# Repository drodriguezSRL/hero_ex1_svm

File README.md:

# HERO Explorer 1 Rover - Service Module (SVM)

The following contains all the design files (i.e., kiCad project files) for the PCBs inside the service module. That includes the Power Supply Unit (PSU), Power Distribution Unit (PDU), and the Rocker Interface Unit (RIU).  3D graphics files are also included (.step and .stl).

## Versioning

High-speed Exploration Rover Team, Explorer 1 Service Module SVM Version 1. Rev. 0.

## Authors

* **David Rodriguez** - *Head of the project*
* **Alan Allart** - *Electronics & Low-level developer*

See also a list of contributors

* **Kazuki Nakagoshi** - *Manufacturing & International relationships*
* **Tristan Lecocq** - *Power system*
* **Sayo Sugimori** - *Secretary*
* **Kazuya Yoshida** - *Professor, Space Robotics Lab*

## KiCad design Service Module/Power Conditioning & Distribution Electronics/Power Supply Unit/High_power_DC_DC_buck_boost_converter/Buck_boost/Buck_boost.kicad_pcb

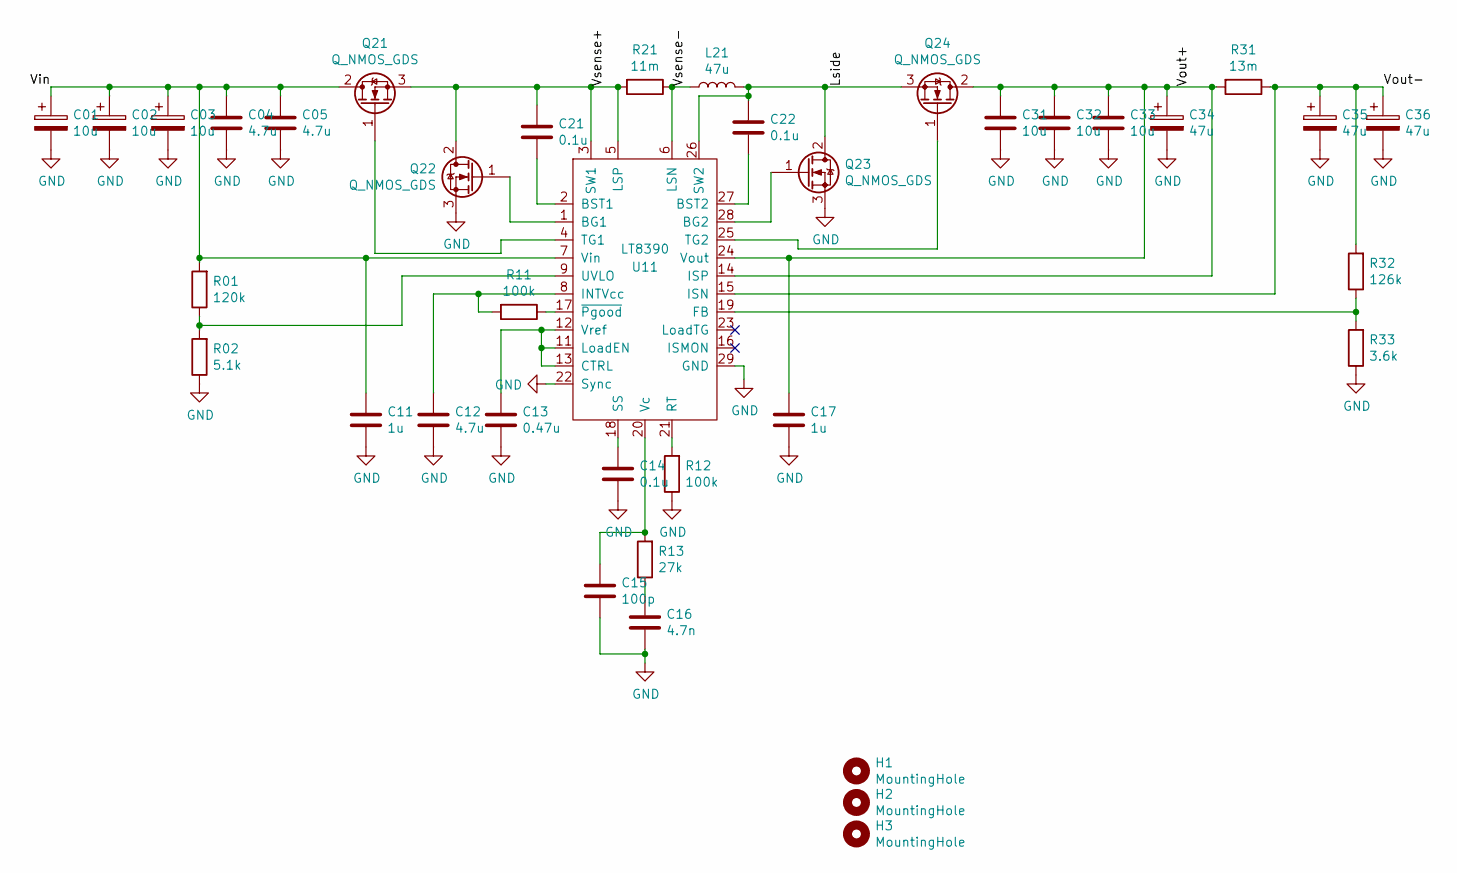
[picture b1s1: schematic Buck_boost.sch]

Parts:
C01, C02, C03: 10u; CP_Elec_8x6.5
C04, C05, C12: 4.7u; C_1206_3216Metric
C11, C17: 1u; C_0805_2012Metric
C13: 0.47u; C_0603_1608Metric
C14: 0.1u; C_0603_1608Metric
C15: 100p; C_0603_1608Metric
C16: 4.7n; C_0603_1608Metric
C21, C22: 0.1u; C_0805_2012Metric
C31, C32, C33: 10u; C_1210_3225Metric
C34, C35, C36: 47u; CP_Elec_10x10.5
H1, H2, H3: MountingHole; MountingHole_2.7mm_M2.5
L21: 47u; PA4344_333ANLT
Q21, Q22, Q23, Q24: Q_NMOS_GDS; DPAK
R01: 120k; R_0603_1608Metric
R02: 5.1k; R_0603_1608Metric
R11, R12: 100k; R_0603_1608Metric
R13: 27k; R_0603_1608Metric
R21: 11m; R_2512_6332Metric
R31: 13m; R_2512_6332Metric
R32: 126k; R_0603_1608Metric
R33: 3.6k; R_0603_1608Metric
U11: LT8390; TSSOP-28-1EP_4.4x9.7mm_P0.65mm

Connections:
/Lside: C22.1, L21.2, Q23.2 (D), Q24.3 (S), U11.26 (SW2)
/Vin: C01.1, C02.1, C03.1, C04.1, C05.1, C11.1, Q21.2 (D), R01.2, U11.7 (Vin)
/Vout+: C17.1, C31.1, C32.1, C33.1, C34.1, Q24.2 (D), R31.2, U11.14 (ISP), U11.24 (Vout)
/Vout-: C35.1, C36.1, R31.1, R32.2, U11.15 (ISN)
/Vsense+: C21.1, Q21.3 (S), Q22.2 (D), R21.2, U11.3 (SW1), U11.5 (LSP)
/Vsense-: L21.1, R21.1, U11.6 (LSN)
GND: C01.2, C02.2, C03.2, C04.2, C05.2, C11.2, C12.2, C13.2, C14.2, C15.2, C16.2, C17.2, C31.2, C32.2, C33.2, C34.2, C35.2, C36.2, Q22.3 (S), Q23.3 (S), R02.1, R12.1, R33.1, U11.22 (Sync), U11.29 (GND)
unnamed: C12.1, R11.2, U11.8 (INTVcc)
unnamed: C13.1, U11.11 (LoadEN), U11.12 (Vref), U11.13 (CTRL)
unnamed: C14.1, U11.18 (SS)
unnamed: C15.1, R13.2, U11.20 (Vc)
unnamed: C16.1, R13.1
unnamed: C21.2, U11.2 (BST1)
unnamed: C22.2, U11.27 (BST2)
unnamed: Q21.1 (G), U11.4 (TG1)
unnamed: Q22.1 (G), U11.1 (BG1)
unnamed: Q23.1 (G), U11.28 (BG2)
unnamed: Q24.1 (G), U11.25 (TG2)
unnamed: R01.1, R02.2, U11.9 (UVLO)
unnamed: R11.1, U11.17 (~Pgood)
unnamed: R12.2, U11.21 (RT)
unnamed: R32.1, R33.2, U11.19 (FB)

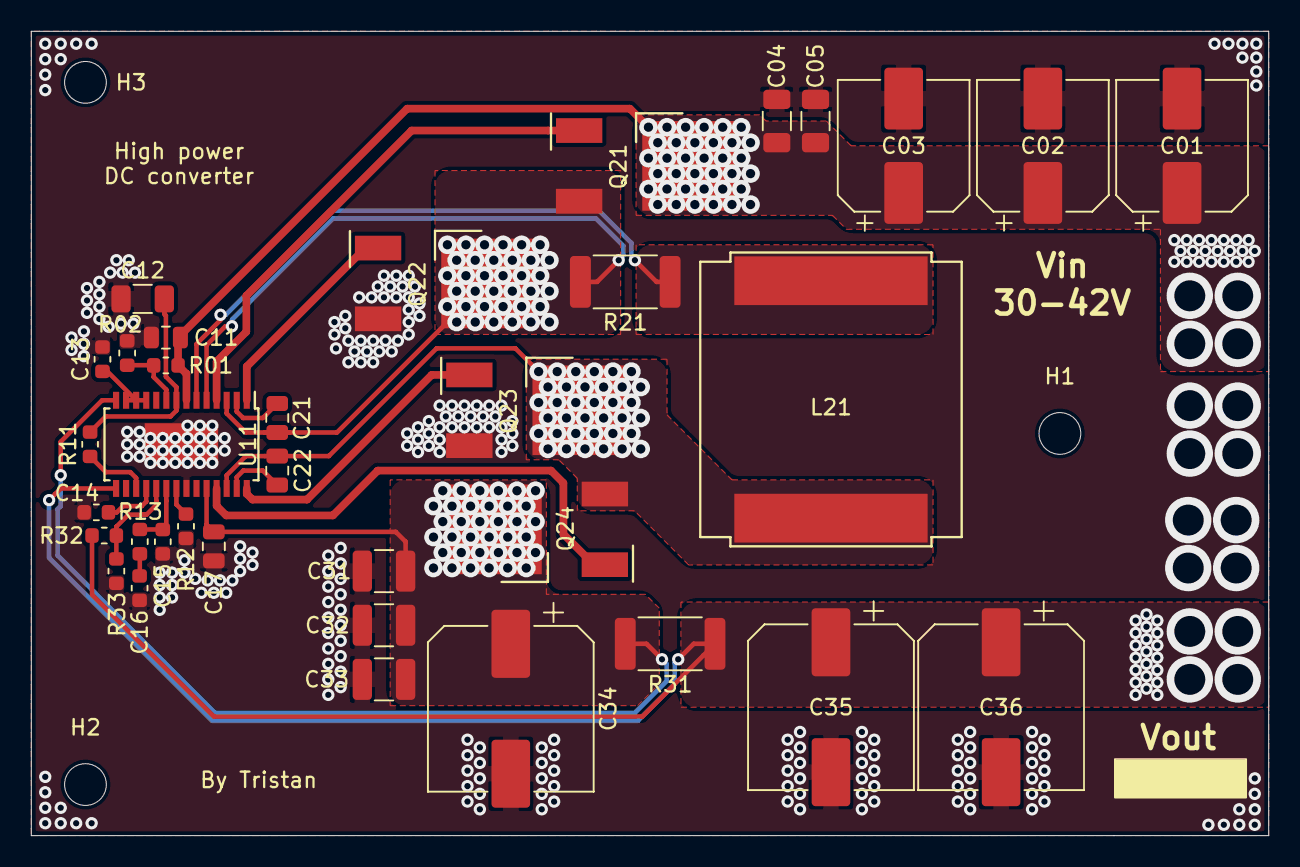
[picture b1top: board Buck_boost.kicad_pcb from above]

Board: 2 copper layers, 80.0 x 52.0 mm, 38 parts (0 on the bottom side), 22 nets.

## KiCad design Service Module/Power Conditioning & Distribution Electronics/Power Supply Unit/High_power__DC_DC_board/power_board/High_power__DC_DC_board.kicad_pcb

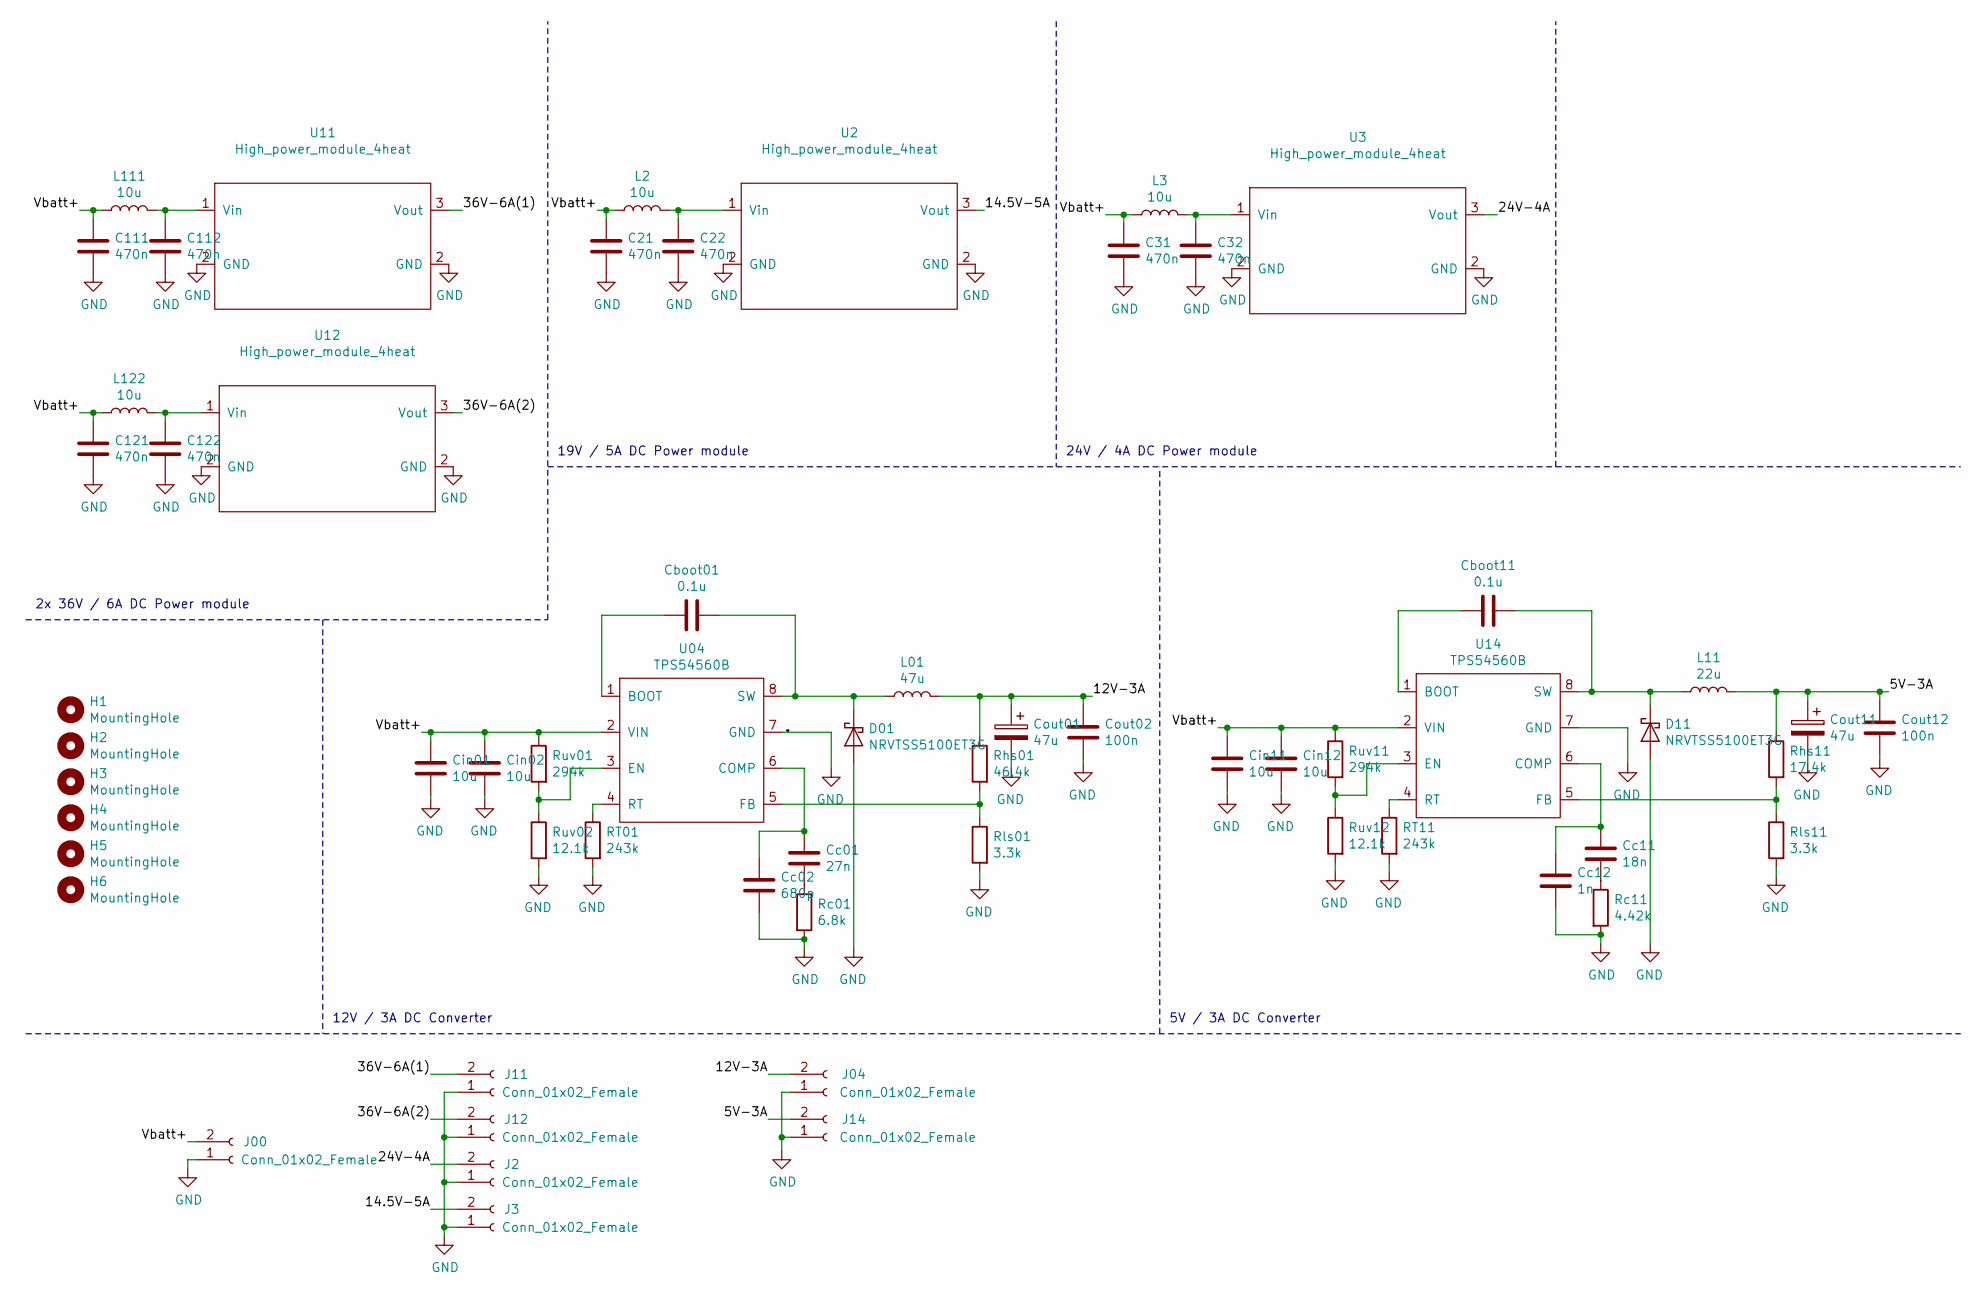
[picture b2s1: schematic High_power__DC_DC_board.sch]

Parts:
C21, C22, C31, C32, C111, C112, C121, C122: 470n; C_1210_3225Metric
Cboot01, Cboot11: 0.1u; C_0805_2012Metric
Cc01: 27n; C_0603_1608Metric
Cc02: 680p; C_0603_1608Metric
Cc11: 18n; C_0603_1608Metric
Cc12: 1n; C_0603_1608Metric
Cin01, Cin02, Cin11, Cin12: 10u; C_1210_3225Metric
Cout01, Cout11: 47u; CP_EIA-7343-40_Kemet-Y
Cout02, Cout12: 100n; C_0805_2012Metric
D01, D11: NRVTSS5100ET3G; D_SMB
H1, H2, H3, H4, H5, H6: MountingHole; MountingHole_3.2mm_M3
J00, J2, J3, J04, J11, J12, J14: Conn_01x02_Female; 172448-0004_Molex_2channel_horizontal
L01: 47u; 177CDMCC-DS
L2, L3: 10u; PA4341-XXXNLT
L11: 22u; 125CDMCCDS
L111, L122: 10u; 744373965100
RT01, RT11: 243k; R_0603_1608Metric
Rc01: 6.8k; R_0603_1608Metric
Rc11: 4.42k; R_0603_1608Metric
Rhs01: 46.4k; R_0603_1608Metric
Rhs11: 17.4k; R_0603_1608Metric
Rls01, Rls11: 3.3k; R_0603_1608Metric
Ruv01, Ruv11: 294k; R_0603_1608Metric
Ruv02, Ruv12: 12.1k; R_0603_1608Metric
U2, U3, U11, U12: High_power_module_4heat; DC_buck_boost_conv
U04, U14: TPS54560B; TPS54560BDDA

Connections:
/5V-3A: Cout11.1, Cout12.1, J14.2, L11.1, Rhs11.1
/12V-3A: Cout01.1, Cout02.1, J04.2, L01.1, Rhs01.1
/14.5V-5A: J3.2, U2.3 (Vout)
/24V-4A: J2.2, U3.3 (Vout)
/36V-6A(1): J11.2, U11.3 (Vout)
/36V-6A(2): J12.2, U12.3 (Vout)
/Vbatt+: C21.1, C31.1, C111.1, C121.1, Cin01.1, Cin02.1, Cin11.1, Cin12.1, J00.2, L2.2, L3.2, L111.2, L122.2, Ruv01.1, Ruv11.1, U04.2 (VIN), U14.2 (VIN)
GND: C21.2, C22.2, C31.2, C32.2, C111.2, C112.2, C121.2, C122.2, Cc02.1, Cc12.1, Cin01.2, Cin02.2, Cin11.2, Cin12.2, Cout01.2, Cout02.2, Cout11.2, Cout12.2, D01.2 (A), D11.2 (A), J00.1, J2.1, J3.1, J04.1, J11.1, J12.1, J14.1, RT01.2, RT11.2, Rc01.2, Rc11.2, Rls01.2, Rls11.2, Ruv02.2, Ruv12.2, U2.2 (GND), U3.2 (GND), U04.7 (GND), U04.9 (PAD), U11.2 (GND), U12.2 (GND), U14.7 (GND), U14.9 (PAD)
unnamed: C22.1, L2.1, U2.1 (Vin)
unnamed: C32.1, L3.1, U3.1 (Vin)
unnamed: C112.1, L111.1, U11.1 (Vin)
unnamed: C122.1, L122.1, U12.1 (Vin)
unnamed: Cboot01.1, D01.1 (K), L01.2, U04.8 (SW)
unnamed: Cboot01.2, U04.1 (BOOT)
unnamed: Cboot11.1, D11.1 (K), L11.2, U14.8 (SW)
unnamed: Cboot11.2, U14.1 (BOOT)
unnamed: Cc01.1, Rc01.1
unnamed: Cc01.2, Cc02.2, U04.6 (COMP)
unnamed: Cc11.1, Rc11.1
unnamed: Cc11.2, Cc12.2, U14.6 (COMP)
unnamed: RT01.1, U04.4 (RT)
unnamed: RT11.1, U14.4 (RT)
unnamed: Rhs01.2, Rls01.1, U04.5 (FB)
unnamed: Rhs11.2, Rls11.1, U14.5 (FB)
unnamed: Ruv01.2, Ruv02.1, U04.3 (EN)
unnamed: Ruv11.2, Ruv12.1, U14.3 (EN)

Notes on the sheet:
12V / 3A DC Converter
5V / 3A DC Converter
2x 36V / 6A DC Power module
19V / 5A DC Power module
24V / 4A DC Power module

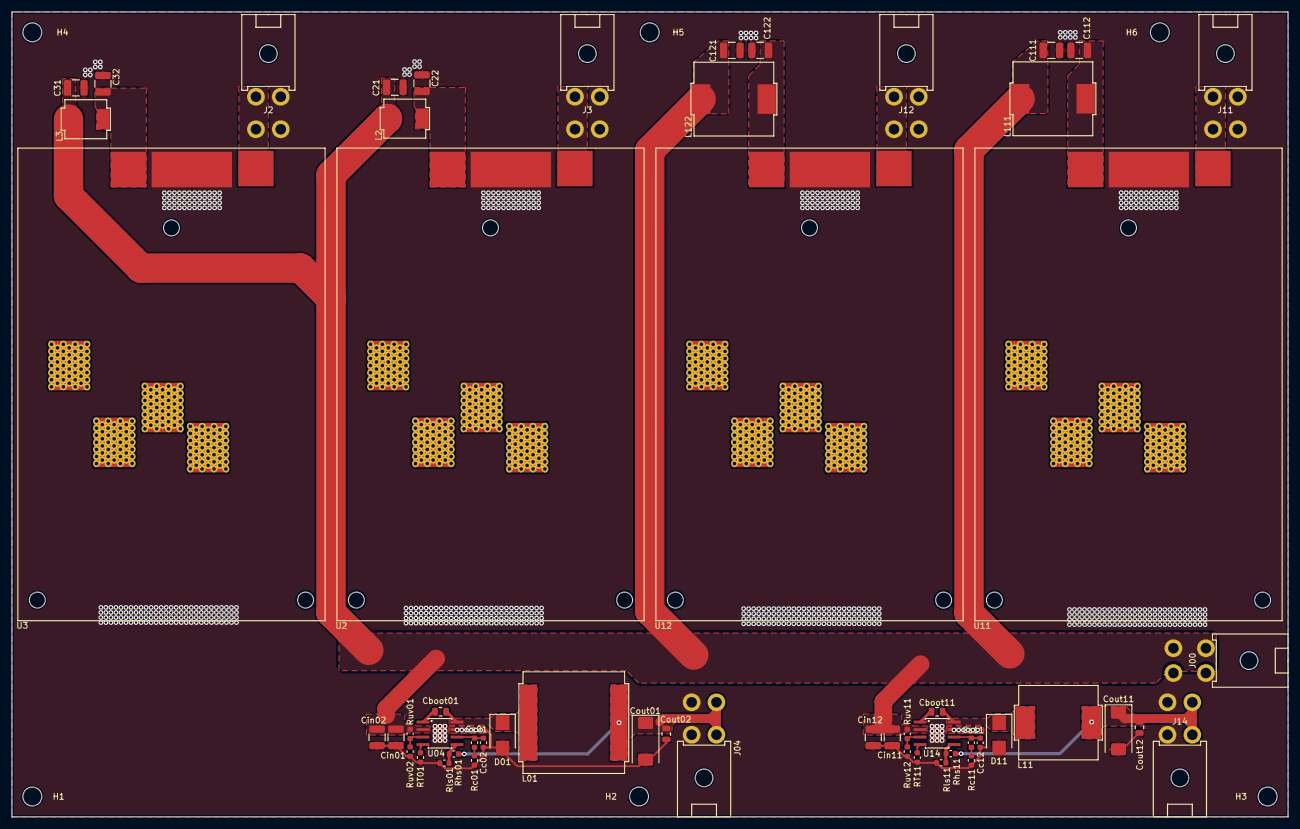
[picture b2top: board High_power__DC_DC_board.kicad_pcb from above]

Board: 2 copper layers, 216.0 x 136.2 mm, 61 parts (0 on the bottom side), 26 nets.

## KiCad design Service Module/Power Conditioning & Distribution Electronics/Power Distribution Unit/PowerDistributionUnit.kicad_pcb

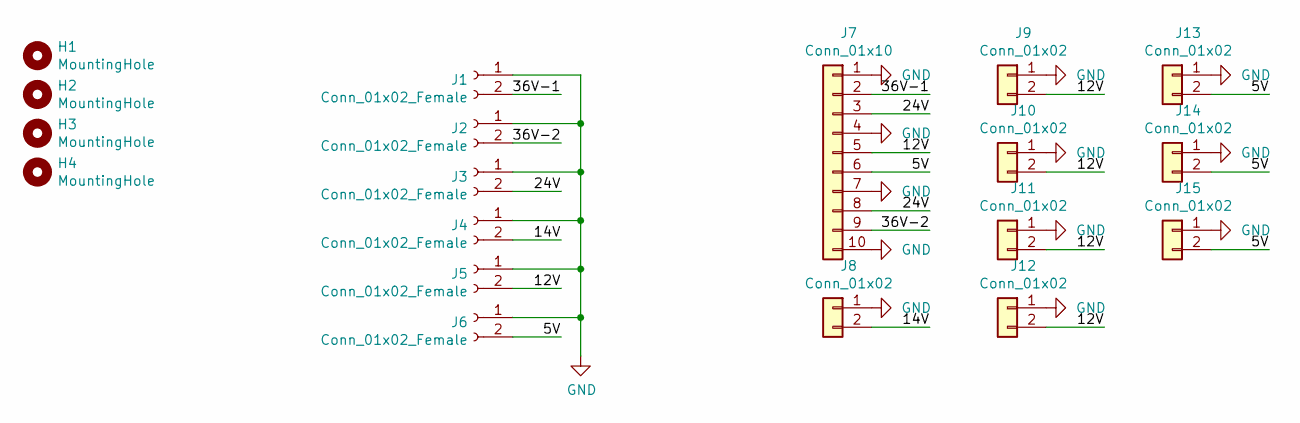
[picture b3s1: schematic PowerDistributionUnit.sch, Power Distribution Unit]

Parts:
H1, H2, H3, H4: MountingHole; MountingHole_3.2mm_M3
J1, J2, J3, J4, J5, J6: Conn_01x02_Female; 172448-0004_Molex_2channel_horizontal
J7: Conn_01x10; JST_VH_B10P-VH
J8: Conn_01x02; JST_VH_B2P-VH
J9, J10, J11, J12, J13, J14, J15: Conn_01x02; JST_XA_B2B-XASK-1

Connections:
/5V: J6.2, J7.6, J13.2, J14.2, J15.2
/12V: J5.2, J7.5, J9.2, J10.2, J11.2, J12.2
/14V: J4.2, J8.2
/24V: J3.2, J7.3, J7.8
/36V-1: J1.2, J7.2
/36V-2: J2.2, J7.9
GND: J1.1, J2.1, J3.1, J4.1, J5.1, J6.1, J7.1, J7.4, J7.7, J7.10, J8.1, J9.1, J10.1, J11.1, J12.1, J13.1, J14.1, J15.1

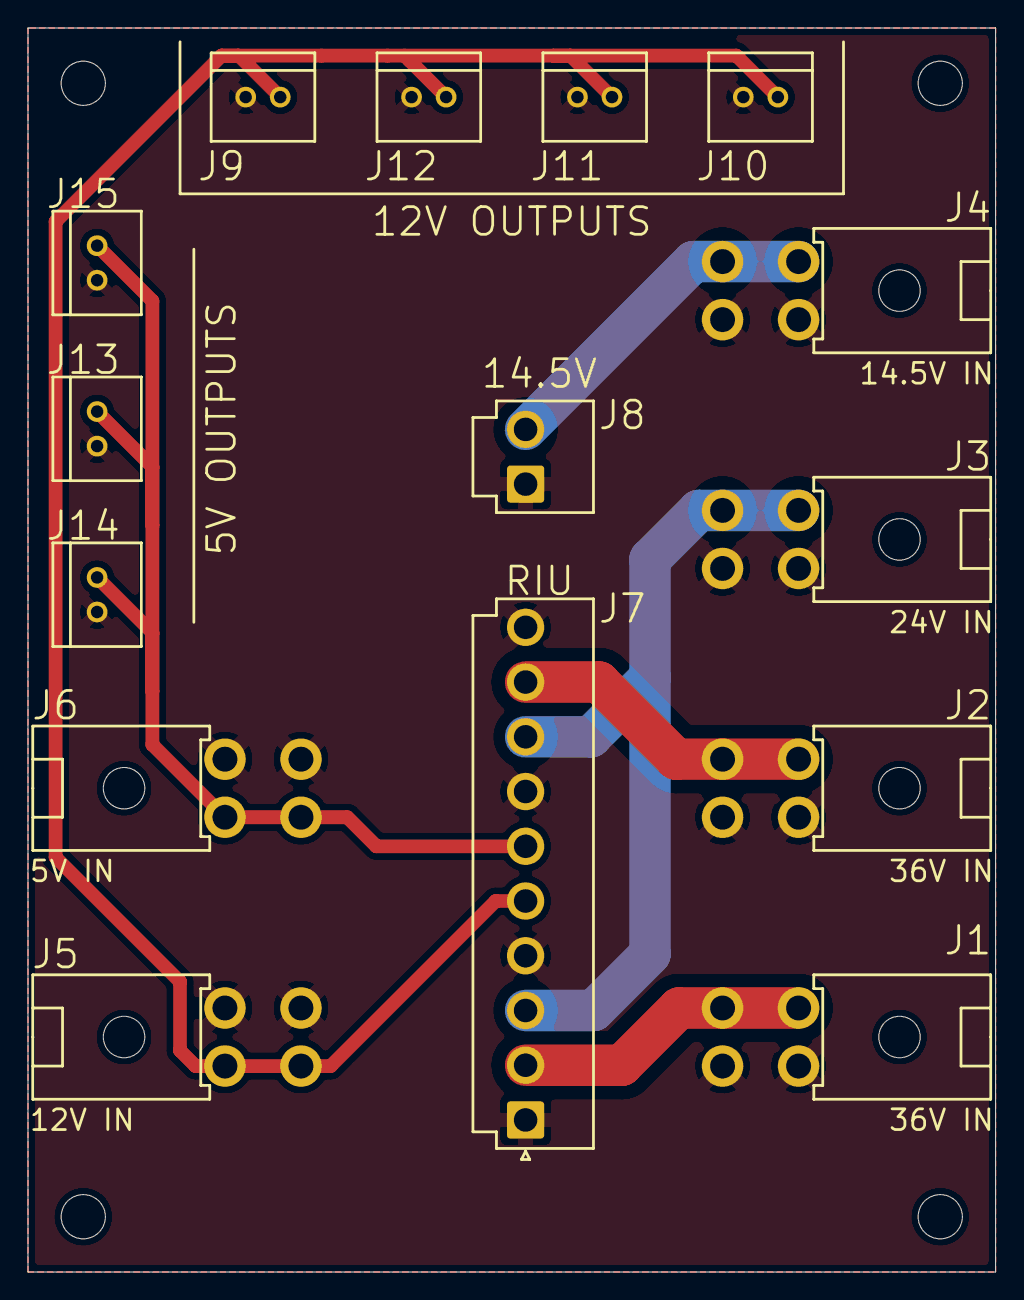
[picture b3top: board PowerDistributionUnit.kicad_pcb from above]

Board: 2 copper layers, 70.0 x 90.0 mm, 19 parts (0 on the bottom side), 7 nets.

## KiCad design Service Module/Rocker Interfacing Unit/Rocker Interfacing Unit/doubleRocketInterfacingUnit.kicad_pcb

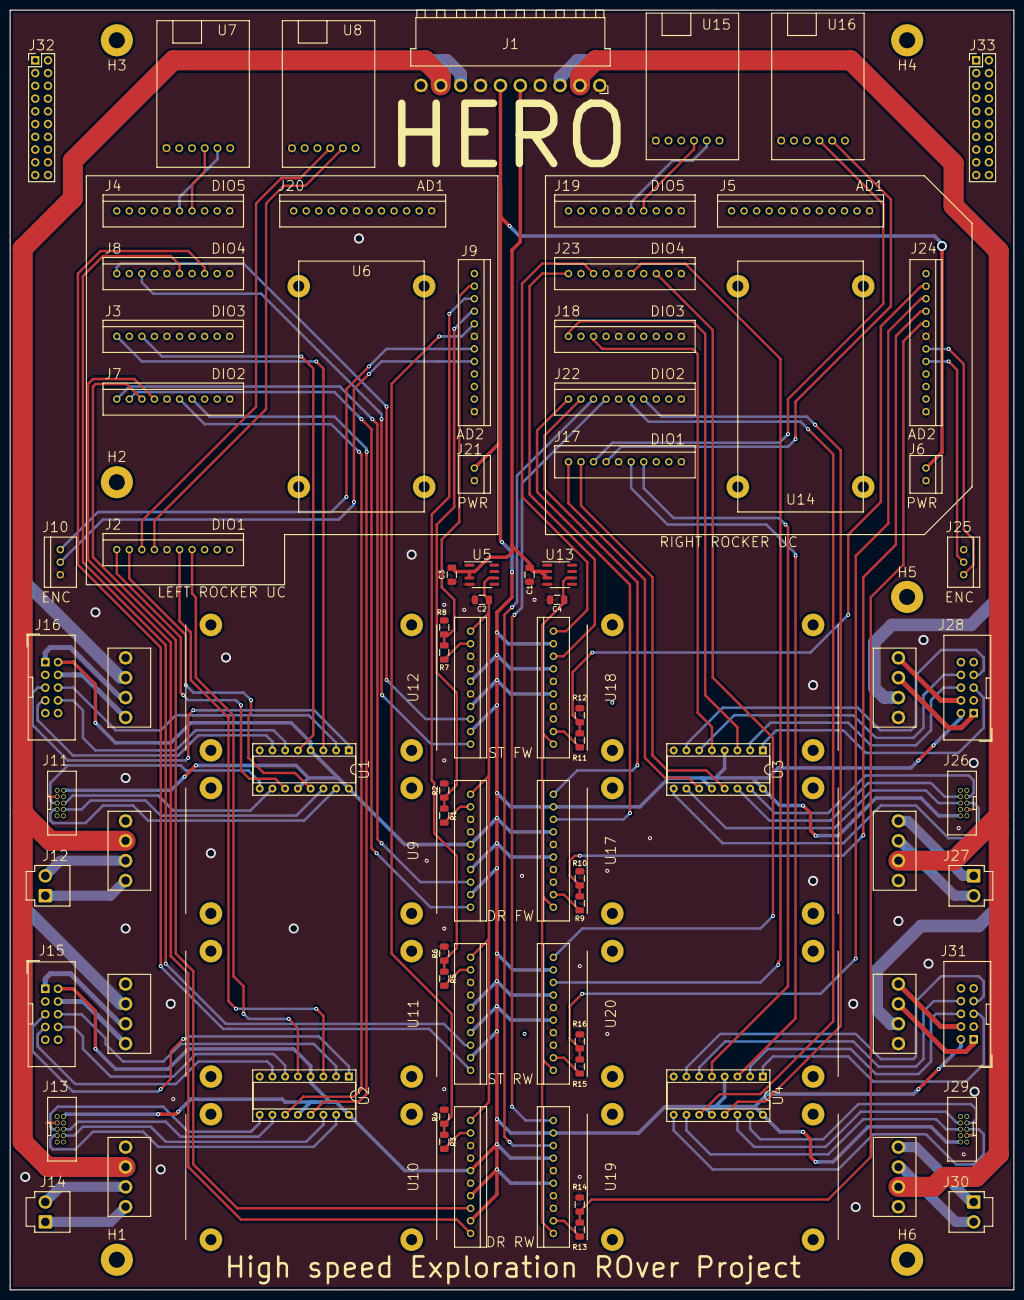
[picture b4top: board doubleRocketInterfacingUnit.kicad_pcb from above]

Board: 2 copper layers, 200.0 x 255.0 mm, 79 parts (0 on the bottom side), 115 nets.

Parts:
C1, C3: 1µF; C_1206_3216Metric
C2, C4: 2µF; C_1206_3216Metric
H1, H2, H3, H4, H5, H6: MountingHole; MountingHole_3.2mm_M3_Pad
J1: Conn_01x10; JST_VH_B10PS-VH
J2, J3, J4, J7, J8, J17, J18, J19, J22, J23: Conn_01x10; JST_XA_B10B-XASK-1
J5, J9, J20, J24: Conn_01x12; JST_XA_B12B-XASK-1
J6, J21: Conn_01x02; JST_XA_B2B-XASK-1
J10, J25: Conn_01x03; JST_XA_B3B-XASK-1
J11, J13, J26, J29: Conn_02x05_Odd_Even; SAMTEC_SHF-105-01-L-D-TH
J12, J14, J27, J30: Conn_01x02; JST_VH_B2P-VH
J15, J16, J28, J31: Conn_02x05_Odd_Even; IDC-Header_2x05_P2.54mm_Vertical
J32, J33: Conn_02x10_Odd_Even; PinHeader_2x10_P2.54mm_Vertical
R1, R3, R5, R7, R9, R11, R13, R15: 4k7; R_1206_3216Metric
R2, R4, R6, R8, R10, R12, R14, R16: 9k1; R_1206_3216Metric
U1, U2, U3, U4: SN75175; DIP-16_W7.62mm_SocketAndIC
U5, U13: LT1461CCS8-5; SOIC-8_3.9x4.9mm_P1.27mm
U6, U14: HiBot-Titech-M4; HibotTitechM4
U7, U8, U15, U16: FTDI-Breakout-Board
U9, U10, U11, U12, U17, U18, U19, U20: HiBot-UM-1XH; HibotUM1XH

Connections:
+5V: J1.6, J6.1, J11.2, J13.2, J15.2, J16.2, J21.1, J26.2, J28.2, J29.2, J31.2, U1.4, U1.12, U1.16, U2.4, U2.12, U2.16, U3.4, U3.12, U3.16, U4.4, U4.12, U4.16, U9.5, U9.7, U9.9, U10.5, U10.7, U10.9, U11.5, U11.7, U11.9, U12.5, U12.7, U12.9, U17.5, U17.7, U17.9, U18.5, U18.7, U18.9, U19.5, U19.7, U19.9, U20.5, U20.7, U20.9
+12V: C1.1, C3.1, J1.5, U5.2, U5.3, U13.2, U13.3
+24V: J1.3, J1.8, U11.13, U12.13, U18.13, U20.13
+36V: J1.2, J1.9, U9.13, U10.13, U17.13, U19.13
/Left Rocker Interface/+3V3A: J9.7, J10.1
/Left Rocker Interface/+5VA: C2.1, U5.6, U9.1, U10.1, U11.1, U12.1
/Left Rocker Interface/CUR_DR_FW: J9.4, R1.1, R2.1
/Left Rocker Interface/CUR_DR_RW: J9.5, R3.1, R4.1
/Left Rocker Interface/CUR_ST_FW: J9.2, R7.1, R8.1
/Left Rocker Interface/CUR_ST_RW: J9.3, R5.1, R6.1
/Left Rocker Interface/ENC_DR_FW_1: J2.1, U1.11
/Left Rocker Interface/ENC_DR_FW_2: J2.2, U1.13
/Left Rocker Interface/ENC_DR_RW_1: J7.6, U2.11
/Left Rocker Interface/ENC_DR_RW_2: J7.7, U2.13
/Left Rocker Interface/ENC_ST_FW_1: J3.1, U1.3
/Left Rocker Interface/ENC_ST_FW_2: J3.3, U1.5
/Left Rocker Interface/ENC_ST_RW_1: J2.6, U2.3
/Left Rocker Interface/ENC_ST_RW_2: J2.7, U2.5
/Left Rocker Interface/Left Driving Motor Driver FW/A: J11.6, U1.10
/Left Rocker Interface/Left Driving Motor Driver FW/B: J11.8, U1.14
/Left Rocker Interface/Left Driving Motor Driver FW/~A~: J11.5, U1.9
/Left Rocker Interface/Left Driving Motor Driver FW/~B~: J11.7, U1.15
/Left Rocker Interface/Left Driving Motor Driver RW/A: J13.6, U2.10
/Left Rocker Interface/Left Driving Motor Driver RW/B: J13.8, U2.14
/Left Rocker Interface/Left Driving Motor Driver RW/~A~: J13.5, U2.9
/Left Rocker Interface/Left Driving Motor Driver RW/~B~: J13.7, U2.15
/Left Rocker Interface/Left Steering Motor Driver FW/A: J16.6, U1.2
/Left Rocker Interface/Left Steering Motor Driver FW/B: J16.8, U1.6
/Left Rocker Interface/Left Steering Motor Driver FW/~A~: J16.5, U1.1
/Left Rocker Interface/Left Steering Motor Driver FW/~B~: J16.7, U1.7
/Left Rocker Interface/Left Steering Motor Driver RW/A: J15.6, U2.2
/Left Rocker Interface/Left Steering Motor Driver RW/B: J15.8, U2.6
/Left Rocker Interface/Left Steering Motor Driver RW/~A~: J15.5, U2.1
/Left Rocker Interface/Left Steering Motor Driver RW/~B~: J15.7, U2.7
/Left Rocker Interface/MOT_DR_FW_1: J7.1, U9.8
/Left Rocker Interface/MOT_DR_FW_2: J7.2, U9.10
/Left Rocker Interface/MOT_DR_RW_1: J7.3, U10.8
/Left Rocker Interface/MOT_DR_RW_2: J7.4, U10.10
/Left Rocker Interface/MOT_ST_FW_1: J8.1, U12.8
/Left Rocker Interface/MOT_ST_FW_2: J8.3, U12.10
/Left Rocker Interface/MOT_ST_RW_1: J8.6, U11.8
/Left Rocker Interface/MOT_ST_RW_2: J8.8, U11.10
/Left Rocker Interface/POS_RK: J9.8, J10.2
/Left Rocker Interface/UART_RX_COM: J4.7, U7.3
/Left Rocker Interface/UART_RX_DBG: J2.3, U8.3
/Left Rocker Interface/UART_TX_COM: J4.6, U7.2
/Left Rocker Interface/UART_TX_DBG: J2.4, U8.2
/Right Rocker Interface/+3V3A: J24.7, J25.1
/Right Rocker Interface/+5VA: C4.1, U13.6, U17.1, U18.1, U19.1, U20.1
/Right Rocker Interface/CUR_DR_FW: J24.4, R9.1, R10.1
/Right Rocker Interface/CUR_DR_RW: J24.5, R13.1, R14.1
/Right Rocker Interface/CUR_ST_FW: J24.2, R11.1, R12.1
/Right Rocker Interface/CUR_ST_RW: J24.3, R15.1, R16.1
/Right Rocker Interface/ENC_DR_FW_1: J17.1, U3.11
/Right Rocker Interface/ENC_DR_FW_2: J17.2, U3.13
/Right Rocker Interface/ENC_DR_RW_1: J22.6, U4.11
/Right Rocker Interface/ENC_DR_RW_2: J22.7, U4.13
/Right Rocker Interface/ENC_ST_FW_1: J18.1, U3.3
/Right Rocker Interface/ENC_ST_FW_2: J18.3, U3.5
/Right Rocker Interface/ENC_ST_RW_1: J17.6, U4.3
/Right Rocker Interface/ENC_ST_RW_2: J17.7, U4.5
/Right Rocker Interface/MOT_DR_FW_1: J22.1, U17.8
/Right Rocker Interface/MOT_DR_FW_2: J22.2, U17.10
/Right Rocker Interface/MOT_DR_RW_1: J22.3, U19.8
/Right Rocker Interface/MOT_DR_RW_2: J22.4, U19.10
/Right Rocker Interface/MOT_ST_FW_1: J23.1, U18.8
/Right Rocker Interface/MOT_ST_FW_2: J23.3, U18.10
/Right Rocker Interface/MOT_ST_RW_1: J23.6, U20.8
/Right Rocker Interface/MOT_ST_RW_2: J23.8, U20.10
/Right Rocker Interface/POS_RK: J24.8, J25.2
/Right Rocker Interface/Right Driving Motor Driver FW/A: J26.6, U3.10
/Right Rocker Interface/Right Driving Motor Driver FW/B: J26.8, U3.14
/Right Rocker Interface/Right Driving Motor Driver FW/~A~: J26.5, U3.9
/Right Rocker Interface/Right Driving Motor Driver FW/~B~: J26.7, U3.15
/Right Rocker Interface/Right Driving Motor Driver RW/A: J29.6, U4.10
/Right Rocker Interface/Right Driving Motor Driver RW/B: J29.8, U4.14
/Right Rocker Interface/Right Driving Motor Driver RW/~A~: J29.5, U4.9
/Right Rocker Interface/Right Driving Motor Driver RW/~B~: J29.7, U4.15
/Right Rocker Interface/Right Steering Motor Driver FW/A: J28.6, U3.2
/Right Rocker Interface/Right Steering Motor Driver FW/B: J28.8, U3.6
/Right Rocker Interface/Right Steering Motor Driver FW/~A~: J28.5, U3.1
/Right Rocker Interface/Right Steering Motor Driver FW/~B~: J28.7, U3.7
/Right Rocker Interface/Right Steering Motor Driver RW/A: J31.6, U4.2
/Right Rocker Interface/Right Steering Motor Driver RW/B: J31.8, U4.6
/Right Rocker Interface/Right Steering Motor Driver RW/~A~: J31.5, U4.1
/Right Rocker Interface/Right Steering Motor Driver RW/~B~: J31.7, U4.7
/Right Rocker Interface/UART_RX_COM: J19.7, U15.3
/Right Rocker Interface/UART_RX_DBG: J17.3, U16.3
/Right Rocker Interface/UART_TX_COM: J19.6, U15.2
/Right Rocker Interface/UART_TX_DBG: J17.4, U16.2
GND: C1.2, C2.2, C3.2, C4.2, J1.1, J1.4, J1.7, J1.10, J2.5, J2.10, J3.5, J3.10, J4.5, J4.10, J5.6, J5.12, J6.2, J7.5, J7.10, J8.5, J8.10, J9.6, J9.12, J10.3, J11.3, J13.3, J15.3, J16.3, J17.5, J17.10, J18.5, J18.10, J19.5, J19.10, J20.6, J20.12, J21.2, J22.5, J22.10, J23.5, J23.10, J24.6, J24.12, J25.3, J26.3, J28.3, J29.3, J31.3, R2.2, R4.2, R6.2, R8.2, R10.2, R12.2, R14.2, R16.2, U1.8, U2.8, U3.8, U4.8, U5.4, U7.6, U8.6, U9.3, U9.4, U9.6, U9.14, U10.3, U10.4, U10.6, U10.14, U11.3, U11.4, U11.6, U11.14, U12.3, U12.4, U12.6, U12.14, U13.4, U15.6, U16.6, U17.3, U17.4, U17.6, U17.14, U18.3, U18.4, U18.6, U18.14, U19.3, U19.4, U19.6, U19.14, U20.3, U20.4, U20.6, U20.14
unnamed: J12.1, U9.11
unnamed: J12.2, U9.12
unnamed: J14.1, U10.11
unnamed: J14.2, U10.12
unnamed: J15.1, U11.12
unnamed: J15.4, U11.11
unnamed: J16.1, U12.12
unnamed: J16.4, U12.11
unnamed: J27.1, U17.11
unnamed: J27.2, U17.12
unnamed: J28.1, U18.12
unnamed: J28.4, U18.11
unnamed: J30.1, U19.11
unnamed: J30.2, U19.12
unnamed: J31.1, U20.12
unnamed: J31.4, U20.11
unnamed: R1.2, U9.2
unnamed: R3.2, U10.2
unnamed: R5.2, U11.2
unnamed: R7.2, U12.2
unnamed: R9.2, U17.2
unnamed: R11.2, U18.2
unnamed: R13.2, U19.2
unnamed: R15.2, U20.2

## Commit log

2020-05-18 All files uploaded
